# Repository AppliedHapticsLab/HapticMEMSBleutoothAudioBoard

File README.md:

# Bluetooth Audio Boards Project

BM83 BluetoothモジュールとCS4344 DACを使用してMEMSを駆動するデバイスです。

*メイン基板の完成例*

*メインに重ねる基板の完成例*

*サブ基板の完成例*

## 目次

- [プロジェクト概要](#プロジェクト概要)
- [基板構成](#基板構成)
- [技術仕様](#技術仕様)
- [主要機能](#主要機能)
- [使用方法](#使用方法)
- [開発環境](#開発環境)
- [ファイル構成](#ファイル構成)
- [ライセンス](#ライセンス)

## プロジェクト概要

このプロジェクトは、Bluetooth音声受信と高品質DAC出力を組み合わせた音声システムです。メイン基板で受信したBluetooth音声をI2S経由で各サブ基板に分配し、高電圧音声信号として出力します。

## 基板構成

### 1. Main_Board（メイン基板）

メインコントローラとして機能する基板です。

**主要機能:**
- **Bluetooth音声受信**: BM83モジュールによるワイヤレス音声受信
- **I2S信号分配**: Main_Board_sub、Sub_Board上のCS4344 DACへのデータ送信
- **電源管理**: USB充電機能付きLiPoバッテリーシステム
- **ユーザーインターフェース**: 音声停止・再生操作ボタン
- **高電圧音声出力**: DRV2700 + CS4344による高電圧音声信号生成

**主要IC:**
- BM83: Bluetoothオーディオモジュール
- CS4344: 24-bit/192kHz ステレオDAC
- DRV2700: 高電圧アンプドライバー

**電源仕様:**
- LiPoバッテリー駆動
- USB充電対応
- 昇圧回路搭載（5V供給）

### 2. Main_Board_sub（メインサブ基板）

メイン基板と同サイズの基板で、DAC機能を担当します。

**特徴:**
- CS4344 DAC搭載
- Main_Boardと同一フォームファクター
- I2S信号受信による音声出力

### 3. Sub_Board（サブ基板）

コンパクトサイズの基板で、DAC機能を担当します。

**特徴:**
- CS4344 DAC搭載
- 小型フォームファクター
- I2S信号受信による音声出力
- 省スペース設置に最適

## システム構成

```
Bluetooth Device
    ↓ Bluetooth Audio
Main_Board (BM83)
    ↓ I2S Signal Distribution
    ├─→ Main_Board_sub (CS4344 DAC) → Audio Output
    └─→ Sub_Board (CS4344 DAC) → Audio Output
```

## 技術仕様

| 項目 | 仕様 |
|------|------|
| Bluetoothチップ | BM83 |
| DAC | CS4344 (24-bit/192kHz) |
| アンプドライバー | DRV2700 |
| 電源 | LiPoバッテリー + USB充電 |
| 音声インターフェース | I2S |
| 昇圧回路 | 5V出力 |

## 主要機能

### 音声処理
- Bluetooth A2DPプロファイル対応
- 高品質24-bit/192kHz DAC出力
- 低レイテンシー音声伝送
- 高電圧音声信号生成

### 電源管理
- LiPoバッテリー駆動
- USB充電システム
- 効率的な昇圧回路
- 低消費電力設計

### ユーザーインターフェース
- 再生/停止ボタン
- シンプルな操作性
- 直感的なコントロール

## 使用方法

### 初期設定
```bash
# リポジトリをクローン
git clone https://github.com/yourusername/bluetooth-audio-boards.git
cd bluetooth-audio-boards
```

- 以下のURLを参考にBM83用のツールソフトをダウンロード・設定する
- URL：https://www.zep.co.jp/kzenyouji/article/z-bm83-da2/

### 基本操作
1. **電源投入**: LiPoバッテリー接続 or USB給電
2. **ペアリング**: 電源投入時に自動的にペアリングモード
3. **音声再生**: Bluetoothデバイスから音声を送信
4. **コントロール**: 基板上のボタンで再生/停止

## 開発環境

### 必要なツール
- PCB設計ソフトウェア
- はんだ付け用具
- 測定器具（オシロスコープ、マルチメーター）

### 推奨開発環境
- Eagle CAD または Fusion360
- 温度制御はんだごて
- デジタルマルチメーター

## ファイル構成

```
/
├── 1.Main_Board/                 # メイン基板設計ファイル
│   ├── Main_Board.brd         
│   ├── Main_Board.sch
│   └── Main_Board_3D.stl
├── 2.Main_Board_sub/            # メインサブ基板設計ファイル
│   ├── Main_Board_sub.brd         
│   ├── Main_Board_sub.sch
│   └── Main_Board_sub_3D.stl
├── 3.Sub_Board/                 # サブ基板設計ファイル
│   ├── Sub_Board.brd         
│   ├── Sub_Board.sch
│   └── Sub_Board_3D.stl
├── images/                      # プロジェクト画像
├── LICENSE                      # ライセンスファイル
├── OptionFile.hex　　　　　　　　# BM83用の設定ファイル
└── README.md                   # このファイル
```

## 謝辞
参考にさせていただいたサイトになります．
- https://www.zep.co.jp/kzenyouji/article/z-bm83-da2/
- https://cotechworks.ltt.jp/2024/08/15/post-1609/

## ライセンス

このプロジェクトは MIT ライセンスの下で公開されています。詳細は [LICENSE](LICENSE) ファイルを参照してください。

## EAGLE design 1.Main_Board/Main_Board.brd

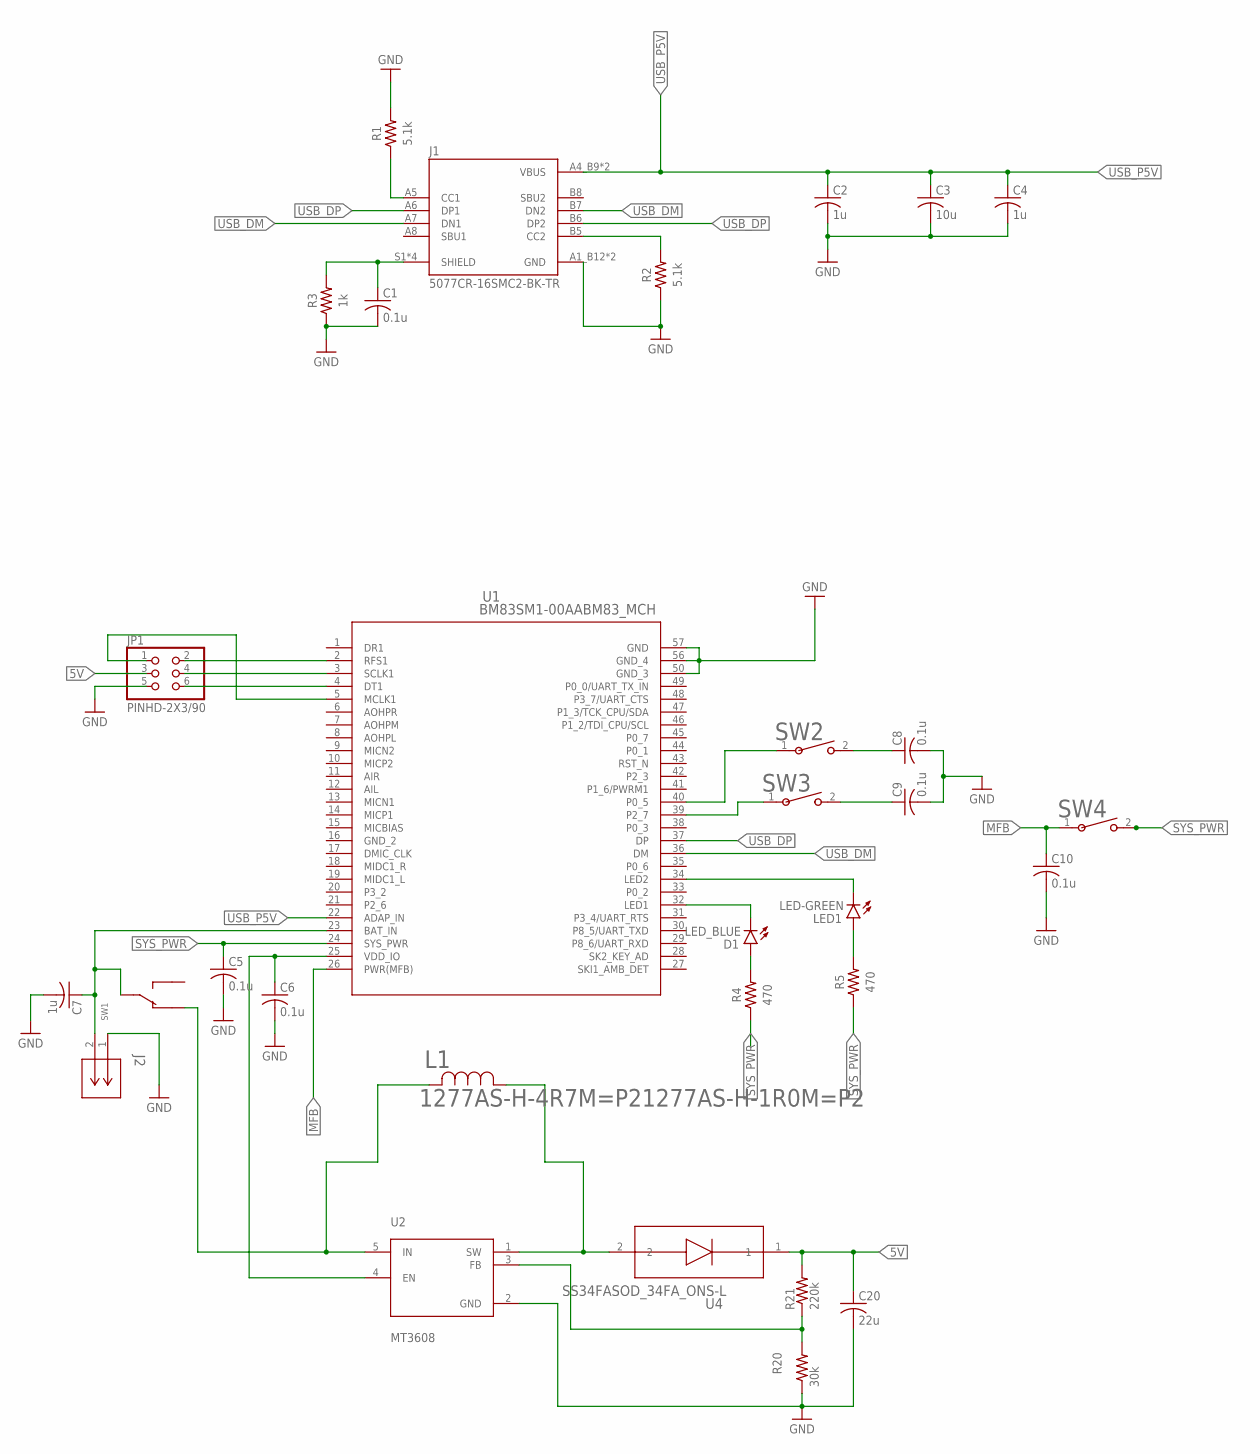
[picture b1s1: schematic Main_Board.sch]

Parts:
C1, C5, C6, C8, C9, C10: 0.1u; CAPC1608X85
C2, C4, C7: 1u; CAPC1608X85
C3: 10u; CAPC1608X85
C20: 22u; CAPC3216X135
D1: LED_BLUE; LEDC1608X39N_B
J1: 5077CR-16SMC2-BK-TR; NELTRON_5077CR-16SMC2-BK-TR
J2: S2B-PH-K-S(LF)(SN); CONN_S2B-PH-K-S_JST
JP1: PINHD-2X3/90; 2X03/90
L1: 1277AS-H-4R7M=P21277AS-H-1R0M=P2; 1277AS-H-1R0M=P2
LED1: LED-GREEN; LEDC1608X39N_G
R1, R2: 5.1k; RESC1608X60
R3: 1k; RESC1608X60
R4, R5: 470; RESC1608X60
R20: 30k; RESC1608X60
R21: 220k; RESC1608X60
SW1: MMS124
SW2, SW3, SW4: EVP-AKE31ASW_EVP-AKE31A_PAN; SW_EVP-AKE31A_PAN
U1: BM83SM1-00AABM83_MCH; BM83_MCH
U2: MT3608; SOT95P280X145-6N
U4: SS34FASOD_34FA_ONS-L; SOD_34FA_ONS-L

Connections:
5V: C20.1, JP1.3, R21.2, U4.1
GND: C1.2, C2.2, C3.2, C4.2, C5.2, C6.2, C7.2, C8.2, C9.2, C10.2, C20.2, J1.A1_B12 (GND), J1.B1_A12 (GND), J2.1, JP1.5, R1.2, R2.1, R3.1, R20.1, U1.50 (GND_3), U1.56 (GND_4), U1.57 (GND), U2.2 (GND)
MFB: C10.1, SW4.1, U1.26 (PWR(MFB))
MICBIAS: U1.15 (MICBIAS)
unnamed: J1.A5 (CC1), R1.1
unnamed: J1.B5 (CC2), R2.2
unnamed: C1.1, J1.S1 (SHIELD), J1.S2 (SHIELD), J1.S3 (SHIELD), J1.S4 (SHIELD), R3.2
unnamed: L1.1, U2.1 (SW), U4.2
unnamed: JP1.2, U1.2 (RFS1)
unnamed: JP1.4, U1.3 (SCLK1)
unnamed: JP1.6, U1.4 (DT1)
unnamed: JP1.1, U1.5 (MCLK1)
unnamed: C7.1, J2.2, SW1.3 (2), U1.23 (BAT_IN)
unnamed: SW2.1, U1.40 (P0_5)
unnamed: SW3.1, U1.39 (P2_7)
unnamed: C8.1, SW2.2
unnamed: C9.1, SW3.2
unnamed: R20.2, R21.1, U2.3 (FB)
unnamed: L1.2, SW1.1, U2.5 (IN)
unnamed: C6.1, U1.25 (VDD_IO), U2.4 (EN)
unnamed: D1.1 (C), U1.32 (LED1)
unnamed: D1.2 (A), R4.2
unnamed: LED1.1 (C), U1.34 (LED2)
unnamed: LED1.2 (A), R5.2
SYS_PWR: C5.1, R4.1, R5.1, SW4.2, U1.24 (SYS_PWR)
USB_DM: J1.A7 (DN1), J1.B7 (DN2), U1.36 (DM)
USB_DP: J1.A6 (DP1), J1.B6 (DP2), U1.37 (DP)
USB_P5V: C2.1, C3.1, C4.1, J1.A4_B9 (VBUS), J1.B4_A9 (VBUS), U1.22 (ADAP_IN)

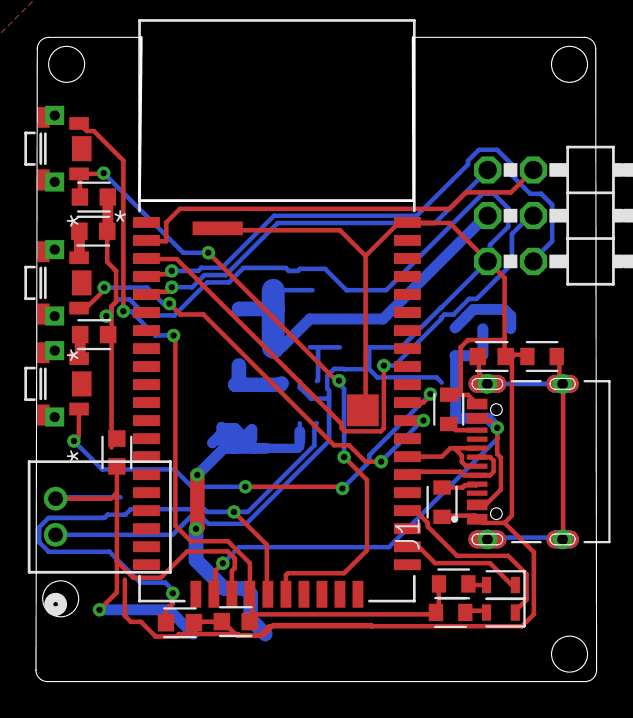
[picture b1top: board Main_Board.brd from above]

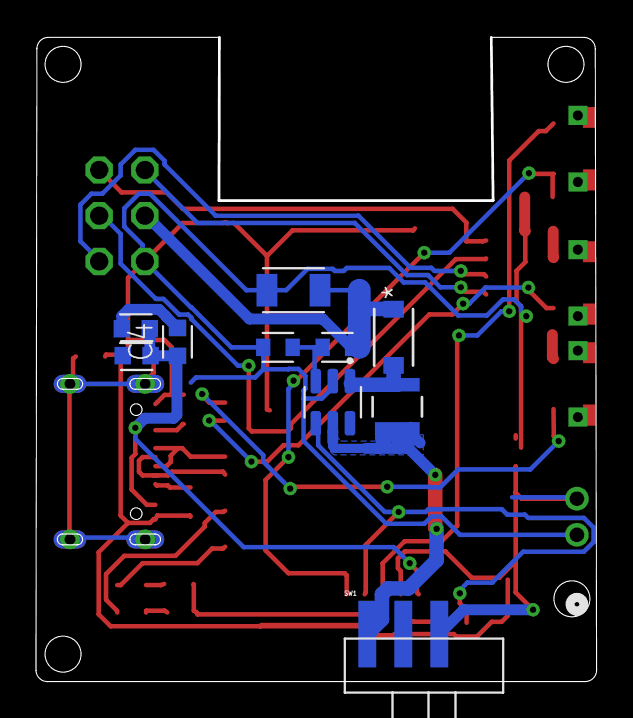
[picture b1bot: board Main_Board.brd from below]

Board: 2 copper layers, 31.0 x 35.7 mm, 31 parts (10 on the bottom side), 27 nets.

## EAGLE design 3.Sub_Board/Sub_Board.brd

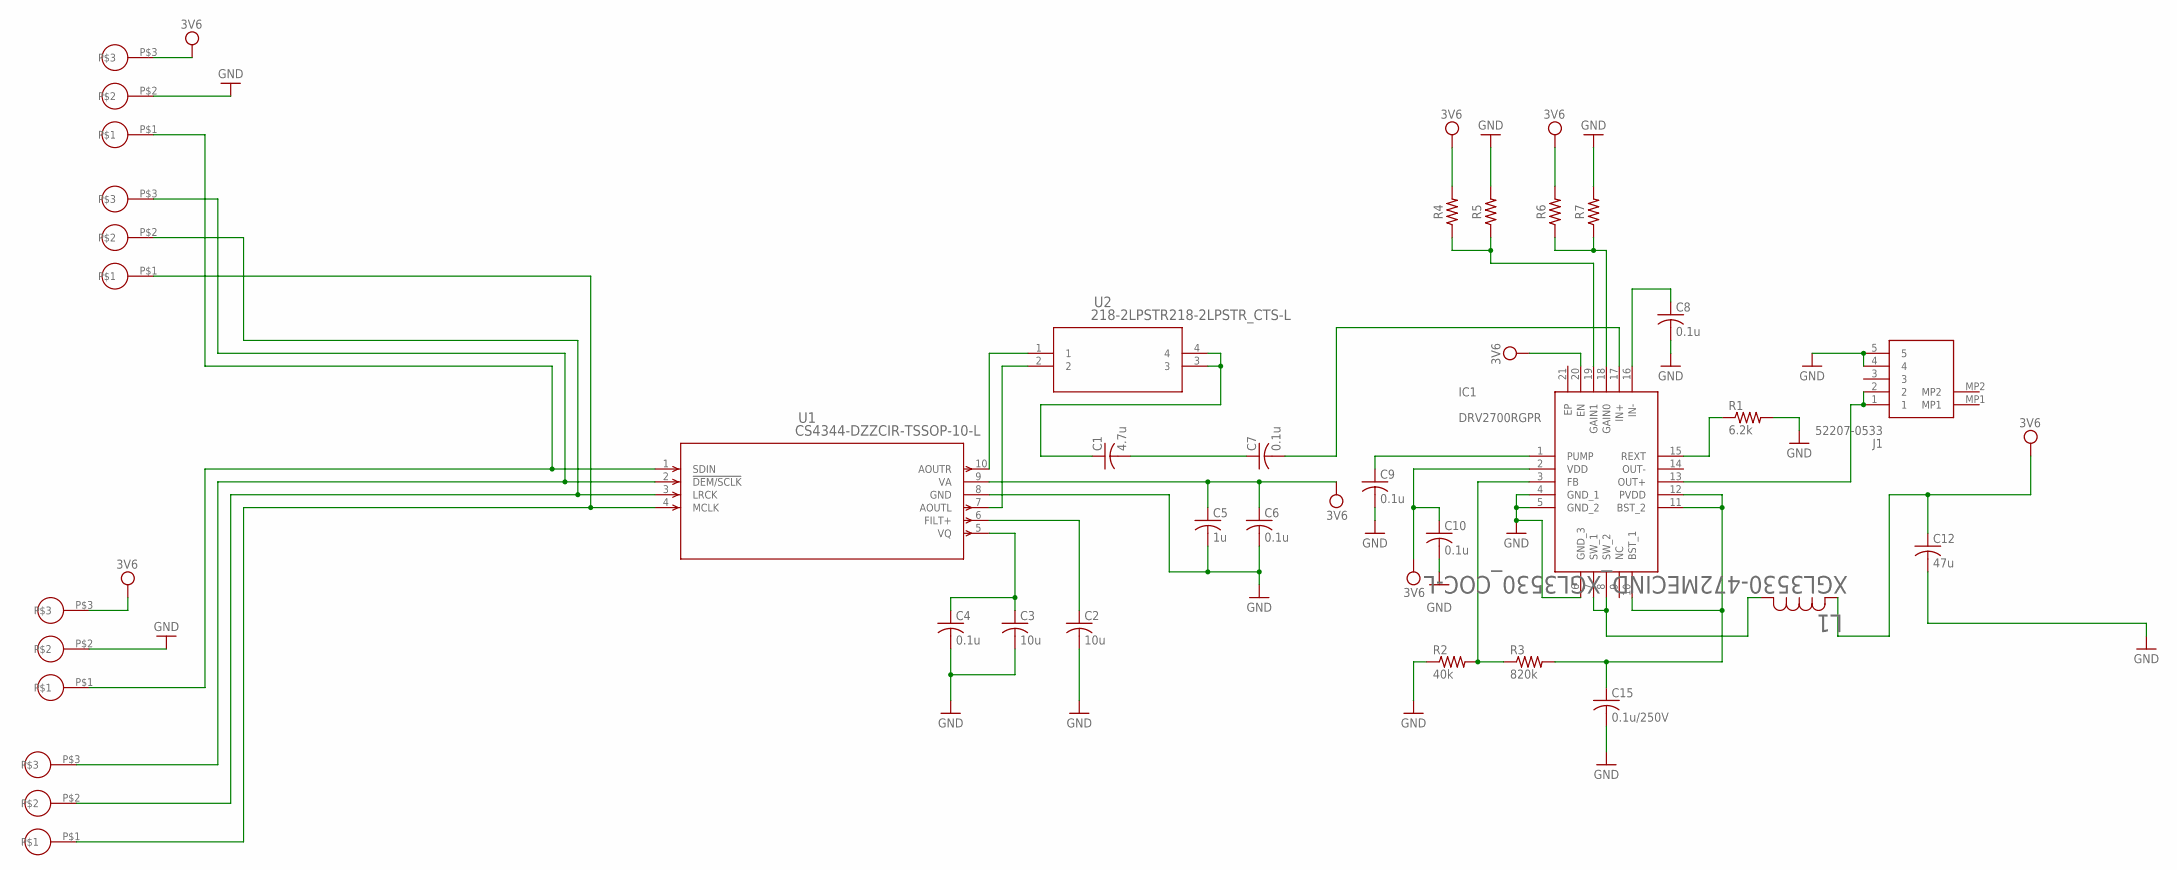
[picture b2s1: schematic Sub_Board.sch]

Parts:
C1: 4.7u; CAPC1608X85
C2, C3: 10u; CAPC1608X85
C4, C6, C7, C8, C9, C10: 0.1u; CAPC1608X85
C5: 1u; CAPC1608X85
C12: 47u; CAPC1608X85
C15: 0.1u/250V; CAPC3216X135
IC1: DRV2700RGPR; QFN50P400X400X100-21N
J1: 52207-0533; 522070533
L1: XGL3530-472MECIND_XGL3530_COC-L; IND_XGL3530_COC-L
R1: 6.2k; RESC1608X60
R2: 40k; RESC1608X60
R3: 820k; RESC1608X60
R4, R5, R6, R7: R-US_CHIP-0603(1608-METRIC); RESC1608X60
U1: CS4344-DZZCIR-TSSOP-10-L; CIR-TSSOP-10-L
U2: 218-2LPSTR218-2LPSTR_CTS-L; 218-2LPSTR_CTS-L
U$1, U$2, U$3, U$4: CONECTOR_MEM

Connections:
3V6: C5.1, C6.1, C10.1, C12.1, IC1.2 (VDD), IC1.20 (EN), L1.2, R4.2, R6.2, U1.9 (VA), U$1.P$3, U$3.P$3
GND: C2.2, C3.2, C4.2, C5.2, C6.2, C8.2, C9.2, C10.2, C12.2, C15.2, IC1.4 (GND_1), IC1.5 (GND_2), IC1.6 (GND_3), J1.4, J1.5, R1.2, R2.1, R5.2, R7.2, U1.8 (GND), U$1.P$2, U$3.P$2
unnamed: C1.1, U2.3, U2.4
unnamed: C1.2, C7.1
unnamed: C7.2, IC1.17 (IN+)
unnamed: C8.1, IC1.16 (IN-)
unnamed: C2.1, U1.6 (FILT+)
unnamed: C3.1, C4.1, U1.5 (VQ)
unnamed: U1.4 (MCLK), U$2.P$1, U$4.P$1
unnamed: C9.1, IC1.1 (PUMP)
unnamed: IC1.3 (FB), R2.2, R3.1
unnamed: C15.1, IC1.10 (BST_1), IC1.11 (BST_2), IC1.12 (PVDD), R3.2
unnamed: IC1.15 (REXT), R1.1
unnamed: IC1.7 (SW_1), IC1.8 (SW_2), L1.1
unnamed: IC1.13 (OUT+), J1.1, J1.2
unnamed: IC1.18 (GAIN0), R6.1, R7.1
unnamed: IC1.19 (GAIN1), R4.1, R5.1
unnamed: U1.10 (AOUTR), U2.1
unnamed: U1.7 (AOUTL), U2.2
unnamed: U1.3 (LRCK), U$2.P$2, U$4.P$2
unnamed: U1.2 (!DEM/SCLK), U$2.P$3, U$4.P$3
unnamed: U1.1 (SDIN), U$1.P$1, U$3.P$1

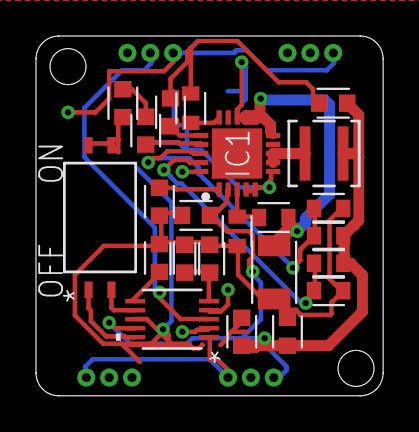
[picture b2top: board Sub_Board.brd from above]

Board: 4 copper layers, 19.3 x 20.0 mm, 28 parts (1 on the bottom side), 22 nets.

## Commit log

2025-06-20 基板等のデータを追加しました
2025-06-20 設定用のファイルを追加しました
2025-06-20 完成型の画像を追加しました

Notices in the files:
README.md:
License: MIT
parts and their libraries:
COPYRIGHT: Copyright (C) 2024 Ultra Librarian. All rights reserved.
